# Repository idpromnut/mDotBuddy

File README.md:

# mDotBuddy
A support PCB that allows for powering and logging of an mDot from Multitech either via on-board FTDI or an external FTDI cable.

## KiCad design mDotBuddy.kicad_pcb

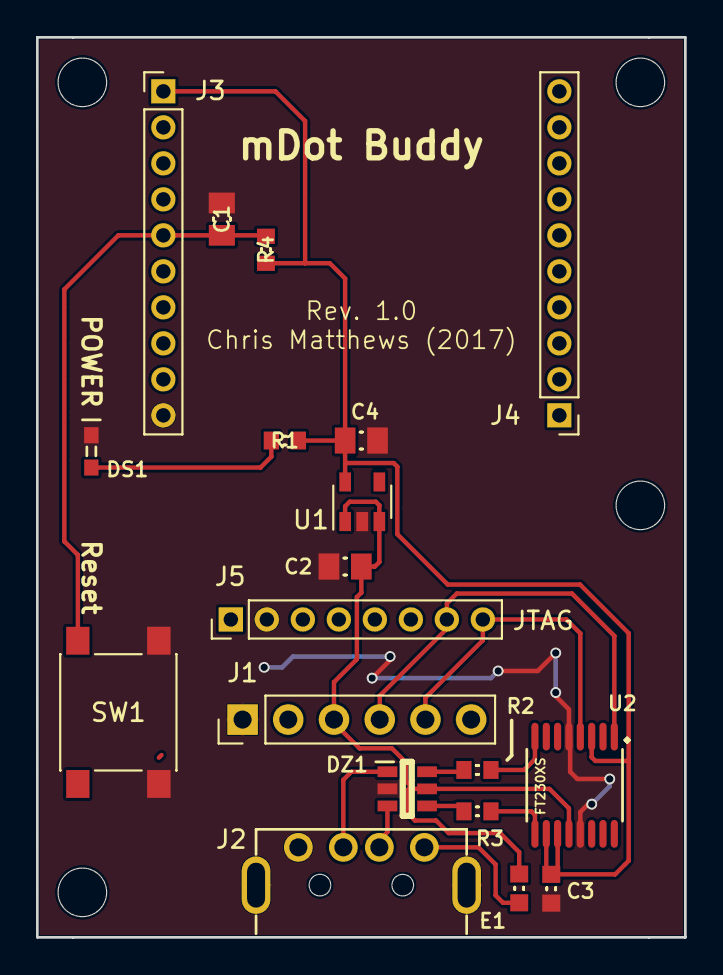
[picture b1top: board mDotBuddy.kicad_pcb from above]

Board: 2 copper layers, 36.0 x 50.0 mm, 19 parts (0 on the bottom side), 14 nets.

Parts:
C1: 0.1uF; CAPC2012X70
C2, C4: 1uF; CAPC2012X70
C3: 100nF; CAPC1608X90
DS1: 3V3_GOOD; LED-0603
DZ1: USBLC6-2SC6; SOT-23-6
E1: BEAD; CAPC1608X90
J1: TTL-232R-3V3; Socket_Strip_Straight_1x06_Pitch2.54mm
J2: USB_A; CONN-UP2-AH-1-TH
J3: mDot_1_10; Socket_Strip_Straight_1x10_Pitch2.00mm
J4: mDot_11_20; Socket_Strip_Straight_1x10_Pitch2.00mm
J5: JTAG; Socket_Strip_Straight_1x08_Pitch2.00mm
R1: 330R; RESC1608X50
R2, R3: 27R; RESC1608X50
R4: 100K; RESC1608X50
SW1: TACT-CK-PTS645-SMD; SW_SPST_PTS645
U1: MIC5504-3.3YM5; SOT-23-5
U2: FT230XS; SOP63P600X160-16

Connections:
+3.3: C3.1, C4.1, J3.1, R1.1, R4.1, U1.5, U2.3, U2.10, U2.11
/RESET: C1.1, J3.5, R4.2, SW1.1
/RX_MDOT: J1.4, J5.7, U2.1
/TX_MDOT: J1.5, J5.8, U2.4
/USB_M: R3.1, U2.9
/USB_P: R2.2, U2.8
GND: C1.2, C2.2, C3.2, C4.2, DS1.1, DZ1.2, J1.1, J2.4, J2.5, J3.10, J5.2, SW1.2, U1.2, U2.5, U2.13
unnamed: DS1.2, R1.2
unnamed: DZ1.1, J2.3
unnamed: DZ1.3, J2.2
unnamed: DZ1.4, R3.2
unnamed: DZ1.6, R2.1
unnamed: E1.1, J2.1
VBUS: C2.1, DZ1.5, E1.2, J1.3, U1.1, U1.3, U2.12

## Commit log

2018-01-02 Rev 1 of the PCB done
